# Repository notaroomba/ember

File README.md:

<h1 align="center">
  <br>
  
  <br>
  Ember
  <br>
</h1>

<h4 align="center">
A high-performance USB-C powered reflow hotplate with Bluetooth connectivity and intelligent temperature control!
</h4>

<div align="center">

</div>

<p align="center">
  <a href="#key-features">Key Features</a> •
  <a href="#pcb">PCB</a> •
  <a href="#case">Case</a> •
  <a href="#heatbed">Heatbed</a> •
  <a href="#credits">Credits</a> •
  <a href="#license">License</a>
</p>

<!--  -->

## Key Features

- **USB-C Power Delivery** up to 100W (20V) using TI's TPS25730D
- **STM32WB55CG** microcontroller with Bluetooth support
- **Large ~~400mm x 400mm~~ ~~200mm x 200mm~~ 120mm x 120mm (for now) flexible heatbed** for big PCB reflow
- **Dual temperature sensing** with MAX6675 thermocouple and PT1000 RTD
- **OLED display** with rotary encoder for easy control and preset management
- **NFC support** for wireless temperature profile transfer and preset storage
- **Gate driver** for precise PWM heatbed control
- **Current and board temperature monitoring** for safety
- **32MB Flash memory** for graphics and data storage
- **Portable design** with custom acrylic / nylon case

## PCB

Designed in KiCad!

### Schematic

### PCB Layout

**Front:**

**Back:**

**Ground Plane:**

**Power Plane:**

Board dimensions: 50mm x 150mm

## Case

Custom designed case in OnShape with practical features:

Features:
- **USB-C port cutout** with flush cable routing
- **Screw terminal access** for heatbed and temperature sensor connections
- **Heatset inserts** for secure assembly with slotted cylindrical head screws
- **High-quality materials**: PA11-HP Nylon base with acrylic top for visibility
- **Rounded corners** for aesthetics and safety

## Heatbed

The heatbed uses JLCPCB's flexible heater technology for cost-effective large-area heating.

The flexible heater connects to the main PCB via screw terminals!

## 3D Renders

## Credits

This project uses:

- [KiCad](https://www.kicad.org/)
- [OnShape](https://www.onshape.com/) for case design
- [Blender](https://www.blender.org/) for 3D renders
- [STM32CubeMX](https://www.st.com/en/development-tools/stm32cubemx.html)
- Inspiration from [this reflow hotplate project](https://github.com/ikajdan/reflow-hot-plate)
- [Arduino GFX Tool](https://arduinogfxtool.netlify.app/) for OLED UI/UX design

## You may also like...

- [Cyberboard](https://github.com/NotARoomba/Cyberboard) – A Raspberry Pi Pico-sized STM32 development board with Bluetooth
- [Trace](https://github.com/NotARoomba/Trace) – A comprehensive PCB ruler with reference footprints
- [CyberCard](https://github.com/NotARoomba/CyberCard) – A Cyberpunk themed NFC hacker card
- [Niveles De Niveles](https://github.com/NotARoomba/NivelesDeNiveles) – Real-time flood alert app
- [Linea](https://github.com/NotARoomba/Linea) – An EMR tablet
- [Tamaki](https://github.com/NotARoomba/Tamaki) – A cute HackPad

## License

MIT

---

> [notaroomba.dev](https://notaroomba.dev) &nbsp;&middot;&nbsp;
> GitHub [@NotARoomba](https://github.com/NotARoomba) &nbsp;&middot;&nbsp;

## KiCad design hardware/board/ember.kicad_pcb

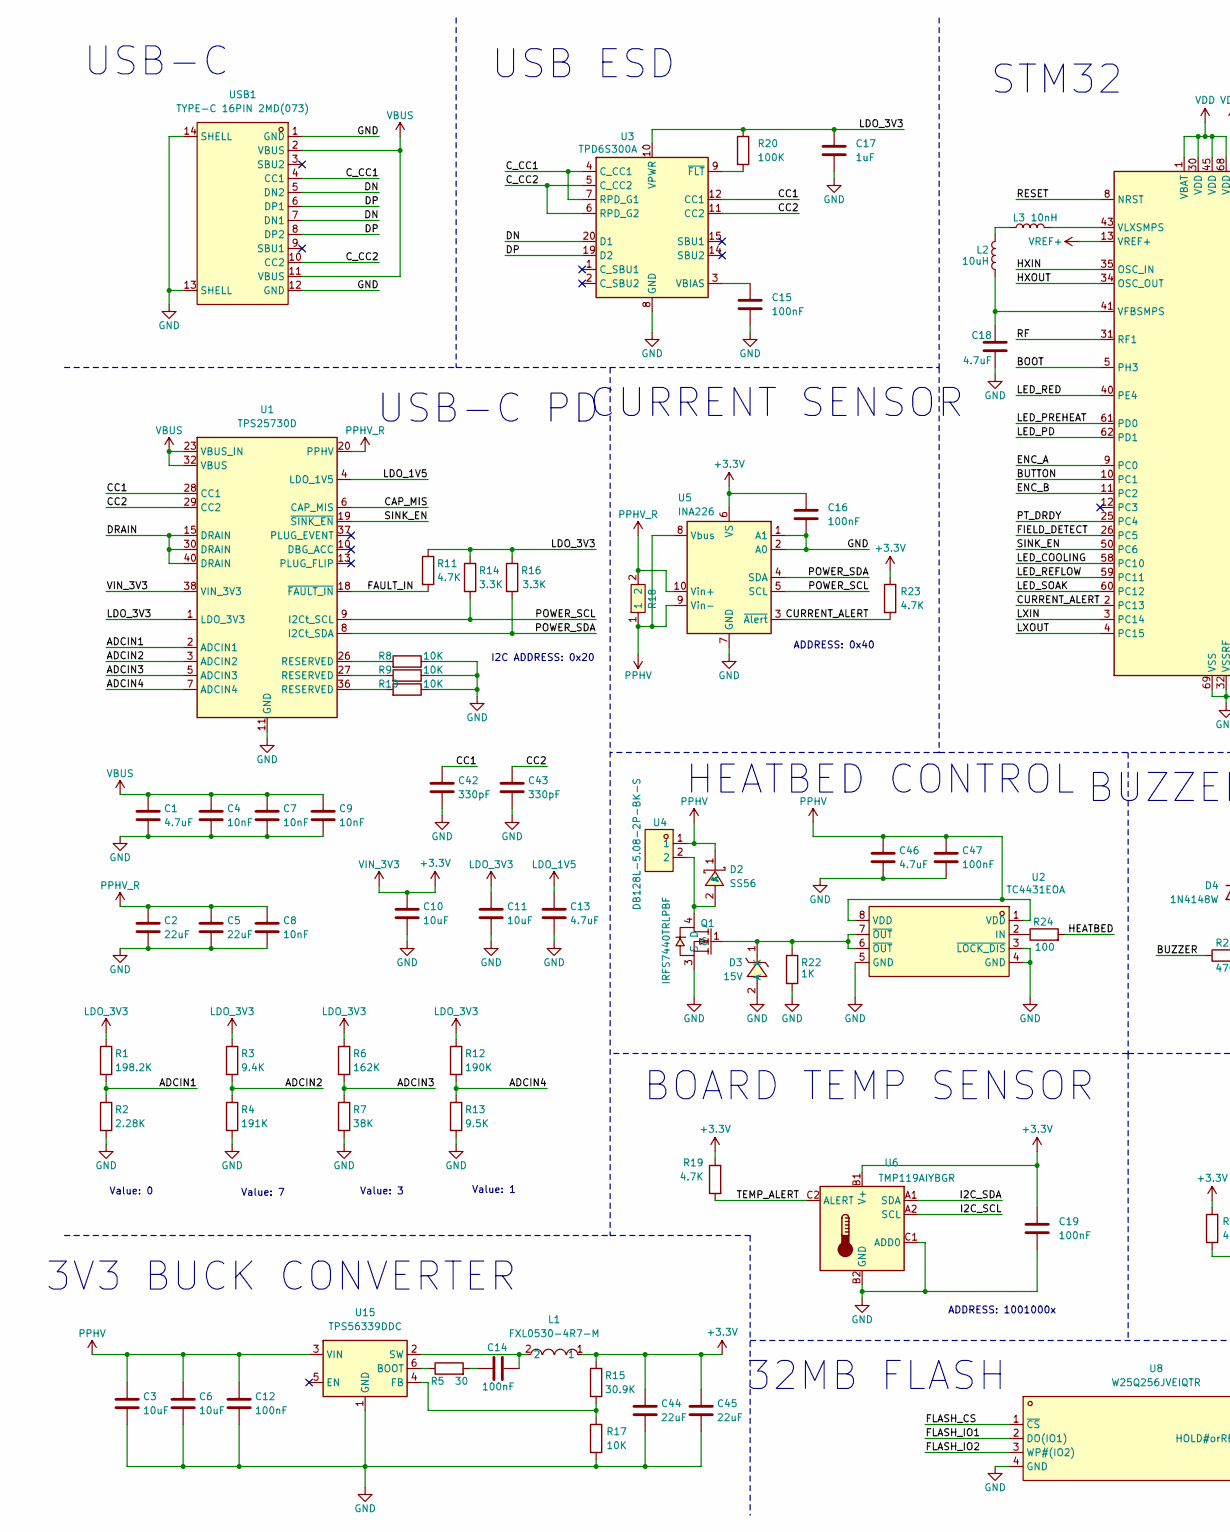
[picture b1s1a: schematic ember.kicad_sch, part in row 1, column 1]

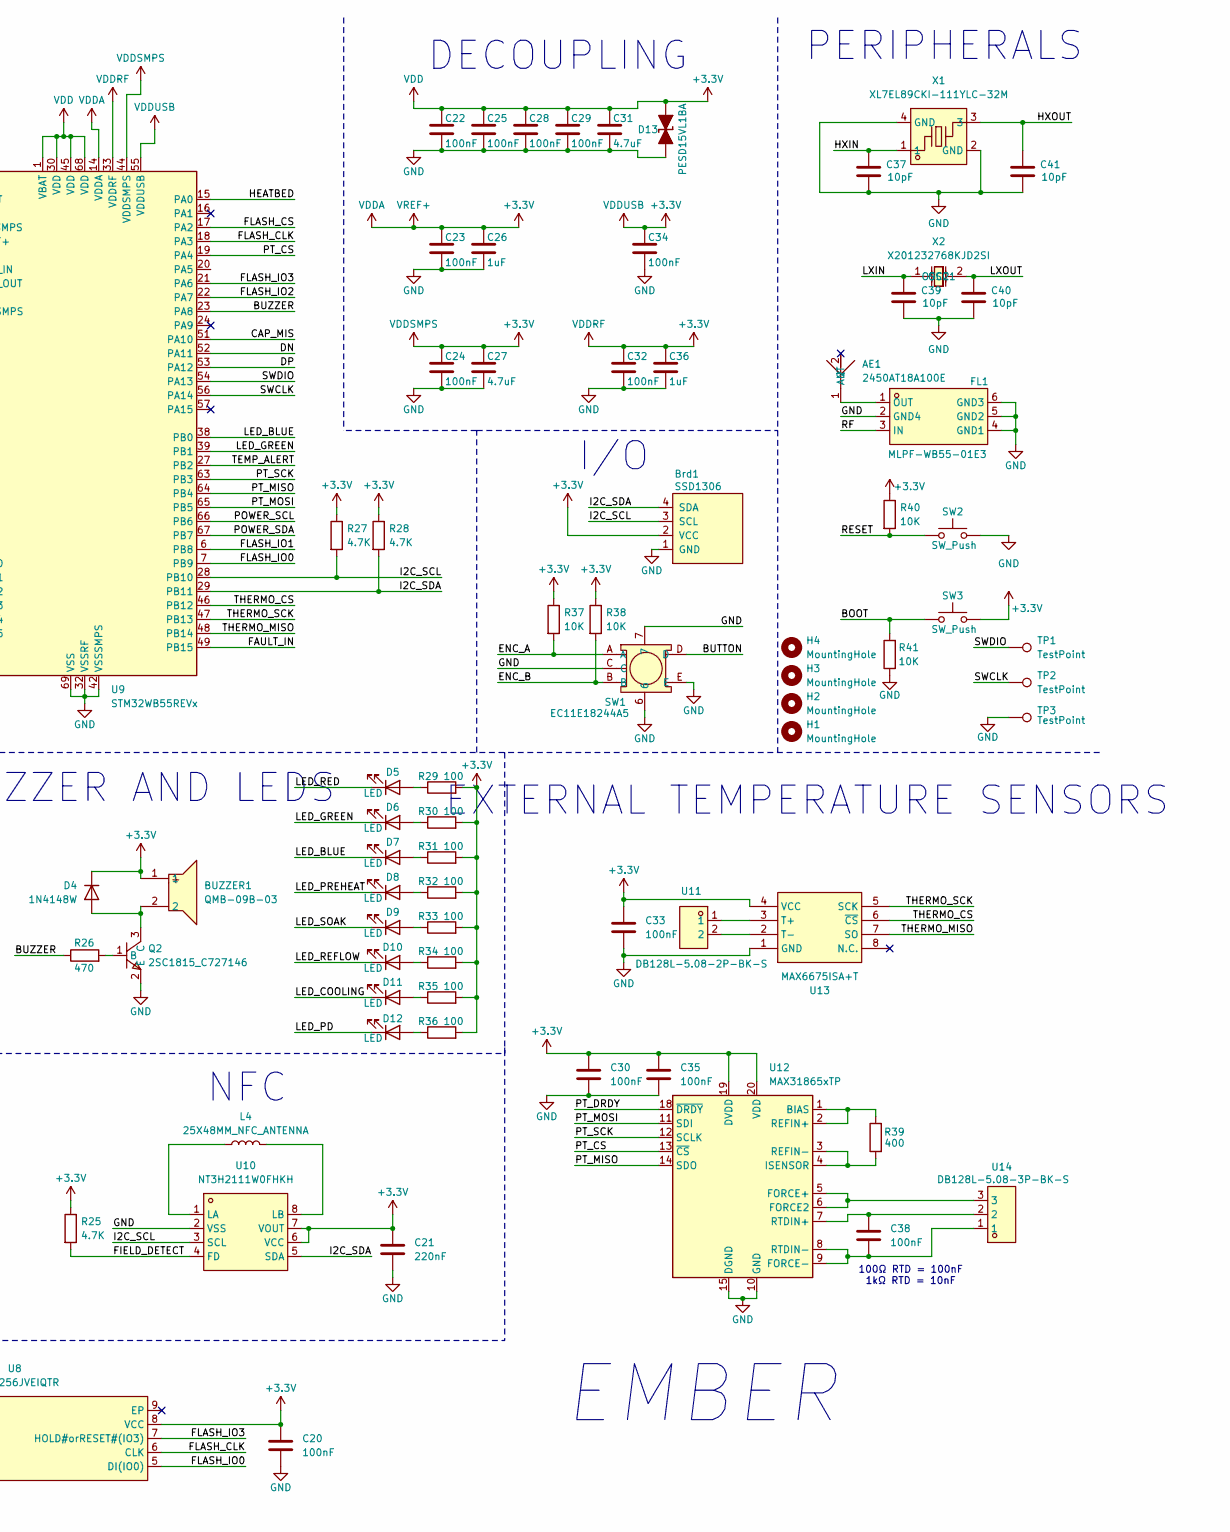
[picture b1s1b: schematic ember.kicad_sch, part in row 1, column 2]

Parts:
AE1: 2450AT18A100E; ANT-SMD_L3.2-W1.6; LCSC Part C89334
BUZZER1: QMB-09B-03; BUZ-TH_BD9.0-P4.00-D0.6-FD; LCSC Part C96256
Brd1: SSD1306; 128x64OLED
C1: 4.7uF; C_0805_2012Metric
C2, C5, C44, C45: 22uF; C_0805_2012Metric
C3, C6: 10uF; C_0805_2012Metric
C4, C7, C9: 10nF; C_0603_1608Metric
C8: 10nF; C_0402_1005Metric
C10, C11: 10uF; C_0402_1005Metric
C12, C47: 100nF; C_0603_1608Metric
C13: 4.7uF; C_0402_1005Metric
C14, C15, C16, C19, C20, C22, C23, C24, C25, C28, C29, C30, C32, C33, C34, C35, C38: 100nF; C_0402_1005Metric
C17: 1uF; C_0402_1005Metric
C18, C27, C31, C46: 4.7uF; C_0603_1608Metric
C21: 220nF; C_0603_1608Metric; LCSC C21120
C26, C36: 1uF; C_0603_1608Metric
C37, C39, C40, C41: 10pF; C_0402_1005Metric
C42, C43: 330pF; C_0402_1005Metric
D2: SS56; SMA_L4.3-W2.6-LS5.2-RD; LCSC Part C65009
D3: 15V; SOD-323_L1.7-W1.3-LS2.6-RD; LCSC Part C19077448
D4: 1N4148W; D_SOD-123
D5: LED; LED_0603_1608Metric; LCSC C965799
D6: LED; LED_0603_1608Metric; LCSC C19171301
D7: LED; LED_0603_1608Metric; LCSC C965807
D8, D9, D10, D11: LED; LED_0603_1608Metric; LCSC C965800
D12: LED; LED_0603_1608Metric; LCSC C2290
D13: PESD15VL1BA; D_SOD-323
FL1: MLPF-WB55-01E3; FILTER-SMD_6P-L1.6-W1.0-P0.50-BL; LCSC Part C2651048
H1, H2, H3, H4: MountingHole; MountingHole_2.2mm_M2
L1: FXL0530-4R7-M; IND-SMD_L5.4-W5.2_FXL0530; LCSC Part C177246
L2: 10uH; L_0603_1608Metric
L3: 10nH; L_0603_1608Metric
L4: 25X48MM_NFC_ANTENNA
Q1: IRFS7440TRLPBF; TO-263-2_L10.0-W9.1-P5.08-LS15.2-BR; LCSC Part C409762
Q2: 2SC1815_C727146; SOT-23-3_L2.9-W1.3-P1.90-LS2.4-BR; LCSC Part C727146
R1: 198.2K; R_0402_1005Metric; LCSC C3013157
R2: 2.28K; R_0402_1005Metric; LCSC C2998174
R3: 9.4K; R_0402_1005Metric; LCSC C852970
R4: 191K; R_0402_1005Metric; LCSC C2998070
R5: 30; R_0402_1005Metric
R6: 162K; R_0402_1005Metric
R7: 38K; R_0402_1005Metric; LCSC C852750
R8, R9, R10, R17, R37, R38, R40, R41: 10K; R_0402_1005Metric
R11, R19, R23, R25, R27, R28: 4.7K; R_0402_1005Metric
R12: 190K; R_0402_1005Metric; LCSC C2998070
R13: 9.5K; R_0402_1005Metric; LCSC C96273
R14, R16: 3.3K; R_0402_1005Metric
R15: 30.9K; R_0402_1005Metric
R18: HOLLR2512-3W-2MR-1%; RES-SMD_L6.4-W3.2-1; LCSC Part C2994640
R20: 100K; R_0402_1005Metric
R22: 1K; R_0402_1005Metric
R24, R29, R30, R31, R32, R33, R34, R35, R36: 100; R_0402_1005Metric
R26: 470; R_0402_1005Metric
R39: 400; R_0805_2012Metric; LCSC C153298
SW1: EC11E18244A5; SW-TH_EC11E18244A5; LCSC Part C255515
SW2, SW3: SW_Push; SW-SMD_L3.9-W3.0-P4.45; LCSC C720477
TP1, TP2, TP3: TestPoint; TestPoint_Pad_1.0x1.0mm
U1: TPS25730D; Texas_REF0038A_WQFN-38-2EP_6x4mm_P0.4
U2: TC4431EOA; SOIC-8_L4.9-W3.9-P1.27-LS6.0-BL; LCSC Part C2909520
U3: TPD6S300A; WQFN-20-1EP_3x3mm_P0.4mm_EP1.7x1.7mm_ThermalVias
U4, U11: DB128L-5.08-2P-BK-S; CONN-TH_2P-P5.08_DB128L-5.08-2P-BK-S; LCSC Part C430601
U5: INA226; VSSOP-10_3x3mm_P0.5mm
U6: TMP119AIYBGR; Texas_DSBGA-6_0.95x1.488mm_Layout2x3_P0.4mm
U8: W25Q256JVEIQTR; WSON-8_L8.0-W6.10-P1.27-BL-EP; LCSC Part C97522
U9: STM32WB55REVx; QFN-68-1EP_8x8mm_P0.4mm_EP6.4x6.4mm
U10: NT3H2111W0FHKH; XQFN-8_L1.6-W1.6-P0.50-BL_NT3H2111W0FHKH; LCSC Part C710403
U12: MAX31865xTP; TQFN-20-1EP_5x5mm_P0.65mm_EP3.25x3.25mm
U13: MAX6675ISA+T; SOIC-8_L5.0-W4.0-P1.27-LS6.0-BL; LCSC Part C16030
U14: DB128L-5.08-3P-BK-S; CONN-TH_3P-P5.08_DB128L-5.08-3P-BK-S; LCSC Part C430602
U15: TPS56339DDC; SOT-23-6
USB1: TYPE-C 16PIN 2MD(073); USB-C-SMD_TYPE-C-6PIN-2MD-073; LCSC Part C2765186
X1: XL7EL89CKI-111YLC-32M; CRYSTAL-SMD_4P-L2.0-W1.6-BL; LCSC Part C2965582
X2: X201232768KJD2SI; OSC-SMD_L2.0-W1.2; LCSC Part C383843

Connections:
+3.3V: BUZZER1.1, Brd1.2 (VCC), C10.1, C16.1, C19.1, C20.1, C21.2, C22.1, C23.1, C24.1, C25.1, C26.1, C27.1, C28.1, C29.1, C30.1, C31.1, C32.1, C33.1, C34.1, C35.1, C36.1, C44.1, C45.1, D4.1 (K), D13.2 (A), L1.1, R15.1, R19.1, R23.1, R25.1, R27.1, R28.1, R29.2, R30.2, R31.2, R32.2, R33.2, R34.2, R35.2, R36.2, R37.1, R38.1, R40.1, SW3.2, U1.38 (VIN_3V3), U5.6 (VS), U6.B1 (V+), U8.8 (VCC), U9.1 (VBAT), U9.13 (VREF+), U9.14 (VDDA), U9.30 (VDD), U9.33 (VDDRF), U9.44 (VDDSMPS), U9.45 (VDD), U9.55 (VDDUSB), U9.68 (VDD), U10.6 (VCC), U10.7 (VOUT), U12.19 (DVDD), U12.20 (VDD), U13.4 (VCC)
/ADCIN1: R1.2, R2.1, U1.2 (ADCIN1)
/ADCIN2: R3.2, R4.1, U1.3 (ADCIN2)
/ADCIN3: R6.2, R7.1, U1.5 (ADCIN3)
/ADCIN4: R12.2, R13.1, U1.7 (ADCIN4)
/BOOT: R41.2, SW3.1, U9.5 (PH3)
/BUTTON: SW1.D, U9.10 (PC1)
/BUZZER: R26.1, U9.23 (PA8)
/CAP_MIS: U1.6 (CAP_MIS), U9.51 (PA10)
/CC1: C42.1, U1.28 (CC1), U3.12 (CC1)
/CC2: C43.1, U1.29 (CC2), U3.11 (CC2)
/CURRENT_ALERT: R23.2, U5.3 (~Alert), U9.2 (PC13)
/C_CC1: U3.4 (C_CC1), U3.7 (RPD_G1), USB1.4 (CC1)
/C_CC2: U3.5 (C_CC2), U3.6 (RPD_G2), USB1.10 (CC2)
/DN: U3.20 (D1), U9.52 (PA11), USB1.5 (DN2), USB1.7 (DN1)
/DP: U3.19 (D2), U9.53 (PA12), USB1.6 (DP1), USB1.8 (DP2)
/DRAIN: U1.15 (DRAIN), U1.30 (DRAIN), U1.40 (DRAIN)
/ENC_A: R37.2, SW1.A, U9.9 (PC0)
/ENC_B: R38.2, SW1.B, U9.11 (PC2)
/FAULT_IN: R11.2, U1.18 (~FAULT_IN), U9.49 (PB15)
/FIELD_DETECT: R25.2, U9.26 (PC5), U10.4 (FD)
/FLASH_CLK: U8.6 (CLK), U9.18 (PA3)
/FLASH_CS: U8.1 (~CS), U9.17 (PA2)
/FLASH_IO0: U8.5 (DI(IO0)), U9.7 (PB9)
/FLASH_IO1: U8.2 (DO(IO1)), U9.6 (PB8)
/FLASH_IO2: U8.3 (WP#(IO2)), U9.22 (PA7)
/FLASH_IO3: U8.7 (HOLD#orRESET#(IO3)), U9.21 (PA6)
/HEATBED: R24.2, U9.15 (PA0)
/HXIN: C37.1, U9.35 (OSC_IN), X1.1
/HXOUT: C41.1, U9.34 (OSC_OUT), X1.3
/I2C_SCL: Brd1.3 (SCL), R27.2, U6.A2 (SCL), U9.28 (PB10), U10.3 (SCL)
/I2C_SDA: Brd1.4 (SDA), R28.2, U6.A1 (SDA), U9.29 (PB11), U10.5 (SDA)
/LED_BLUE: D7.1 (K), U9.38 (PB0)
/LED_COOLING: D11.1 (K), U9.58 (PC10)
/LED_GREEN: D6.1 (K), U9.39 (PB1)
/LED_PD: D12.1 (K), U9.62 (PD1)
/LED_PREHEAT: D8.1 (K), U9.61 (PD0)
/LED_RED: D5.1 (K), U9.40 (PE4)
/LED_REFLOW: D10.1 (K), U9.59 (PC11)
/LED_SOAK: D9.1 (K), U9.60 (PC12)
/LXIN: C39.1, U9.3 (PC14), X2.1 (OSC1)
/LXOUT: C40.1, U9.4 (PC15), X2.2 (OSC2)
/POWER_SCL: R14.2, U1.9 (I2Ct_SCL), U5.5 (SCL), U9.66 (PB6)
/POWER_SDA: R16.2, U1.8 (I2Ct_SDA), U5.4 (SDA), U9.67 (PB7)
/PT_CS: U9.19 (PA4), U12.13 (~CS)
/PT_DRDY: U9.25 (PC4), U12.18 (~DRDY)
/PT_MISO: U9.64 (PB4), U12.14 (SDO)
/PT_MOSI: U9.65 (PB5), U12.11 (SDI)
/PT_SCK: U9.63 (PB3), U12.12 (SCLK)
/RESET: R40.2, SW2.1, U9.8 (NRST)
/RF: FL1.3 (IN), U9.31 (RF1)
/SINK_EN: U1.19 (~SINK_EN), U9.50 (PC6)
/SWCLK: TP2.1, U9.56 (PA14)
/SWDIO: TP1.1, U9.54 (PA13)
/TEMP_ALERT: R19.2, U6.C2 (ALERT), U9.27 (PB2)
/THERMO_CS: U9.46 (PB12), U13.6 (~CS)
/THERMO_MISO: U9.48 (PB14), U13.7 (SO)
/THERMO_SCK: U9.47 (PB13), U13.5 (SCK)
GND: Brd1.1 (GND), C1.2, C2.2, C3.2, C4.2, C5.2, C6.2, C7.2, C8.2, C9.2, C10.2, C11.2, C12.2, C13.2, C15.2, C16.2, C17.2, C18.2, C19.2, C20.2, C21.1, C22.2, C23.2, C24.2, C25.2, C26.2, C27.2, C28.2, C29.2, C30.2, C31.2, C32.2, C33.2, C34.2, C35.2, C36.2, C37.2, C39.2, C40.2, C41.2, C42.2, C43.2, C44.2, C45.2, C46.2, C47.2, D3.2 (A), D13.1 (K), FL1.2 (GND4), FL1.4 (GND1), FL1.5 (GND2), FL1.6 (GND3), Q1.3 (S), Q2.2 (E), R2.2, R4.2, R7.2, R8.1, R9.1, R10.1, R13.2, R17.2, R22.2, R41.1, SW1.6, SW1.7, SW1.C, SW1.E, SW2.2, TP3.1, U1.11 (GND), U1.12 (GND), U1.14 (GND), U1.16 (GND), U1.17 (GND), U1.31 (GND), U1.34 (GND), U1.39 (GND), U2.3 (~LOCK_DIS), U2.4 (GND), U2.5 (GND), U3.8 (GND), U3.13 (GND), U3.16 (GND), U3.17 (GND), U3.18 (GND), U3.21 (GND), U5.1 (A1), U5.2 (A0), U5.7 (GND), U6.B2 (GND), U6.C1 (ADD0), U8.4 (GND), U8.9 (EP), U9.32 (VSSRF), U9.42 (VSSSMPS), U9.69 (VSS), U10.2 (VSS), U12.10 (GND), U12.15 (DGND), U12.16 (GND), U12.21 (GND), U13.1 (GND), U15.1 (GND), USB1.1 (GND), USB1.12 (GND), USB1.13 (SHELL), USB1.14 (SHELL), X1.2 (GND), X1.4 (GND)
LDO_1V5: C13.1, U1.4 (LDO_1V5)
LDO_3V3: C11.1, C17.1, R1.1, R3.1, R6.1, R11.1, R12.1, R14.1, R16.1, R20.1, U1.1 (LDO_3V3), U3.10 (VPWR)
unnamed: AE1.1 (ANT), FL1.1 (OUT)
unnamed: C14.1, R5.2
unnamed: D2.2 (A), Q1.4 (D), U4.2
unnamed: D3.1 (K), Q1.1 (G), R22.1, U2.6 (~OUT), U2.7 (~OUT)
unnamed: BUZZER1.2, D4.2 (A), Q2.3 (C)
unnamed: D5.2 (A), R29.1
unnamed: D6.2 (A), R30.1
unnamed: D7.2 (A), R31.1
unnamed: D8.2 (A), R32.1
unnamed: D9.2 (A), R33.1
unnamed: D10.2 (A), R34.1
unnamed: D11.2 (A), R35.1
unnamed: D12.2 (A), R36.1
unnamed: L2.1, L3.2
unnamed: Q2.1 (B), R26.2
unnamed: R8.2, U1.26 (RESERVED)
unnamed: R9.2, U1.27 (RESERVED)
unnamed: R10.2, U1.36 (RESERVED)
unnamed: R24.1, U2.2 (IN)
unnamed: C15.1, U3.3 (VBIAS)
unnamed: R20.2, U3.9 (~FLT)
unnamed: C18.1, L2.2, U9.41 (VFBSMPS)
unnamed: L3.1, U9.43 (VLXSMPS)
unnamed: L4.1, U10.1 (LA)
unnamed: L4.2, U10.8 (LB)
unnamed: R39.1, U12.1 (BIAS), U12.2 (REFIN+)
unnamed: U12.5 (FORCE+), U12.6 (FORCE2), U14.3
unnamed: C38.2, U12.8 (RTDIN-), U12.9 (FORCE-), U14.1
unnamed: R39.2, U12.3 (REFIN-), U12.4 (ISENSOR)
unnamed: C38.1, U12.7 (RTDIN+), U14.2
unnamed: U11.1, U13.3 (T+)
unnamed: U11.2, U13.2 (T-)
unnamed: R5.1, U15.6 (BOOT)
unnamed: R15.2, R17.1, U15.4 (FB)
unnamed: C14.2, L1.2, U15.2 (SW)
PPHV: C3.1, C6.1, C12.1, C46.1, C47.1, D2.1 (K), R18.1, U2.1 (VDD), U2.8 (VDD), U4.1, U5.8 (Vbus), U5.9 (Vin-), U15.3 (VIN)
PPHV_R: C2.1, C5.1, C8.1, R18.2, U1.20 (PPHV), U5.10 (Vin+)
VBUS: C1.1, C4.1, C7.1, C9.1, U1.23 (VBUS_IN), U1.32 (VBUS), USB1.2 (VBUS), USB1.11 (VBUS)

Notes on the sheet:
I/O
EXTERNAL TEMPERATURE SENSORS
PERIPHERALS
EMBER
BUZZER AND LEDS
USB-C
100Ω RTD = 100nF 1kΩ RTD = 10nF
USB ESD
USB-C PD
Value: 7
Value: 1
BOARD TEMP SENSOR
DECOUPLING
NFC
32MB FLASH
CURRENT SENSOR
ADDRESS: 0x40
3V3 BUCK CONVERTER
ADDRESS: 1001000x
HEATBED CONTROL
Value: 0
I2C ADDRESS: 0x20
STM32
Value: 3

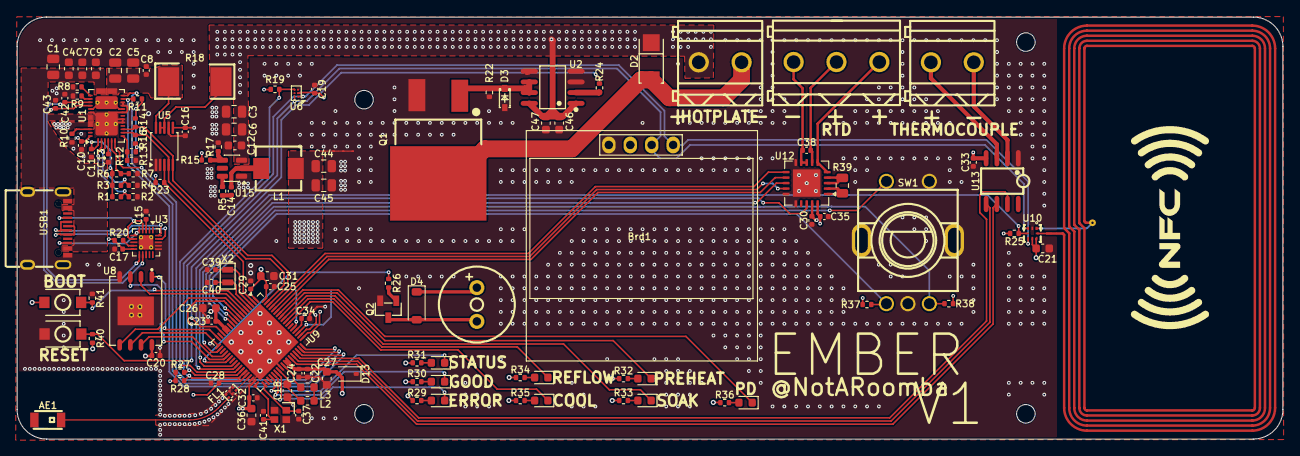
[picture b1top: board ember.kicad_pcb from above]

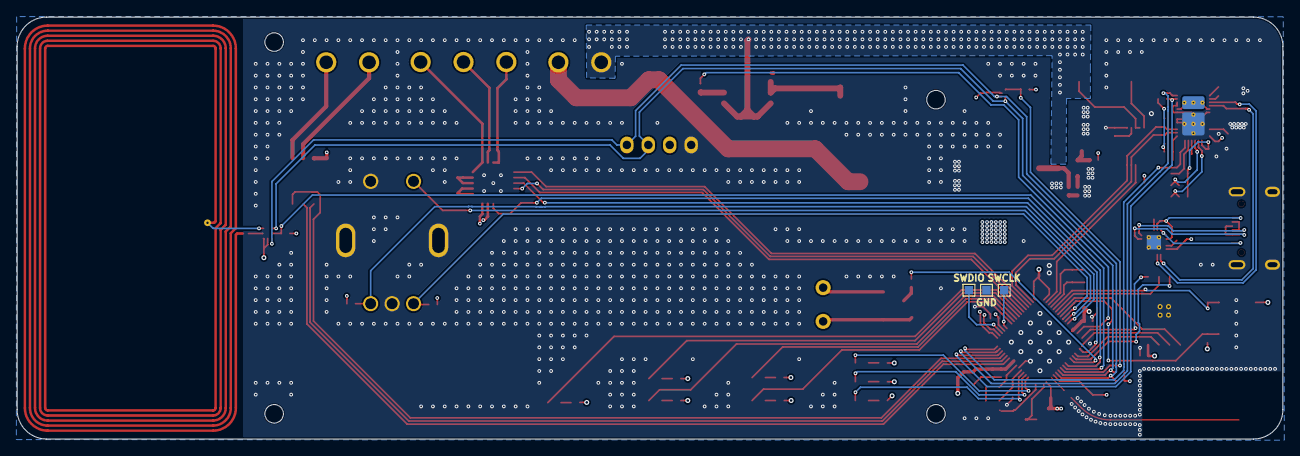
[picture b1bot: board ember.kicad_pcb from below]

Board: 4 copper layers, 150.0 x 50.0 mm, 136 parts (3 on the bottom side), 97 nets.

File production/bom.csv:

Designator,Footprint,Quantity,Value,LCSC Part #
AE1,ANT-SMD_L3.2-W1.6,1,2450AT18A100E,C89334
BRD1,128x64OLED,1,SSD1306,
BUZZER1,BUZ-TH_BD9.0-P4.00-D0.6-FD,1,QMB-09B-03,C96256
C1,0805,1,4.7uF,
"C10, C11",0402,2,10uF,
"C12, C47",0603,2,100nF,
C13,0402,1,4.7uF,
"C14, C15, C16, C19, C20, C22, C23, C24, C25, C28, C29, C30, C32, C33, C34, C35, C38",0402,17,100nF,
C17,0402,1,1uF,
"C18, C27, C31, C46",0603,4,4.7uF,
"C2, C44, C45, C5",0805,4,22uF,
C21,0603,1,220nF,C21120
"C26, C36",0603,2,1uF,
"C3, C6",0805,2,10uF,
"C37, C39, C40, C41",0402,4,10pF,
"C4, C7, C9",0603,3,10nF,
"C42, C43",0402,2,330pF,
C8,0402,1,10nF,
"D10, D11, D8, D9",0603,4,LED,C965800
D12,0603,1,LED,C2290
D13,D_SOD-323,1,PESD15VL1BA,
D2,SMA_L4.3-W2.6-LS5.2-RD,1,SS56,C65009
D3,SOD-323_L1.7-W1.3-LS2.6-RD,1,15V,C19077448
D4,D_SOD-123,1,1N4148W,
D5,0603,1,LED,C965799
D6,0603,1,LED,C19171301
D7,0603,1,LED,C965807
FL1,FILTER-SMD_6P-L1.6-W1.0-P0.50-BL,1,MLPF-WB55-01E3,C2651048
L1,IND-SMD_L5.4-W5.2_FXL0530,1,FXL0530-4R7-M,C177246
L2,0603,1,10uH,
L3,0603,1,10nH,
L4,25X48MM_NFC_ANTENNA,1,25X48MM_NFC_ANTENNA,
Q1,TO-263-2_L10.0-W9.1-P5.08-LS15.2-BR,1,IRFS7440TRLPBF,C409762
Q2,SOT-23-3_L2.9-W1.3-P1.90-LS2.4-BR,1,2SC1815_C727146,C727146
R1,0402,1,198.2K,C3013157
"R10, R17, R37, R38, R40, R41, R8, R9",0402,8,10K,
"R11, R19, R23, R25, R27, R28",0402,6,4.7K,
R12,0402,1,190K,C2998070
R13,0402,1,9.5K,C96273
"R14, R16",0402,2,3.3K,
R15,0402,1,30.9K,
R18,RES-SMD_L6.4-W3.2-1,1,HOLLR2512-3W-2MR-1%,C2994640
R2,0402,1,2.28K,C2998174
R20,0402,1,100K,
R22,0402,1,1K,
"R24, R29, R30, R31, R32, R33, R34, R35, R36",0402,9,100,
R26,0402,1,470,
R3,0402,1,9.4K,C852970
R39,0805,1,400,C153298
R4,0402,1,191K,C2998070
R5,0402,1,30,
R6,0402,1,162K,
R7,0402,1,38K,C852750
SW1,SW-TH_EC11E18244A5,1,EC11E18244A5,C255515
"SW2, SW3",SW-SMD_L3.9-W3.0-P4.45,2,SW_Push,C720477
"TP1, TP2, TP3",TestPoint_Pad_1.0x1.0mm,3,TestPoint,
U1,Texas_REF0038A_WQFN-38-2EP_6x4mm_P0.4,1,TPS25730D,
U10,XQFN-8_L1.6-W1.6-P0.50-BL_NT3H2111W0FHKH,1,NT3H2111W0FHKH,C710403
"U11, U4",CONN-TH_2P-P5.08_DB128L-5.08-2P-BK-S,2,DB128L-5.08-2P-BK-S,C430601
U12,TQFN-20-1EP_5x5mm_P0.65mm_EP3.25x3.25mm,1,MAX31865xTP,
U13,SOIC-8_L5.0-W4.0-P1.27-LS6.0-BL,1,MAX6675ISA+T,C16030
U14,CONN-TH_3P-P5.08_DB128L-5.08-3P-BK-S,1,DB128L-5.08-3P-BK-S,C430602
U15,SOT-23-6,1,TPS56339DDC,
U2,SOIC-8_L4.9-W3.9-P1.27-LS6.0-BL,1,TC4431EOA,C2909520
U3,WQFN-20-1EP_3x3mm_P0.4mm_EP1.7x1.7mm_ThermalVias,1,TPD6S300A,
U5,VSSOP-10_3x3mm_P0.5mm,1,INA226,
U6,Texas_DSBGA-6_0.95x1.488mm_Layout2x3_P0.4mm,1,TMP119AIYBGR,
U8,WSON-8_L8.0-W6.10-P1.27-BL-EP,1,W25Q256JVEIQTR,C97522
U9,QFN-68-1EP_8x8mm_P0.4mm_EP6.4x6.4mm,1,STM32WB55REVx,
USB1,USB-C-SMD_TYPE-C-6PIN-2MD-073,1,TYPE-C 16PIN 2MD(073),C2765186
X1,CRYSTAL-SMD_4P-L2.0-W1.6-BL,1,XL7EL89CKI-111YLC-32M,C2965582
X2,OSC-SMD_L2.0-W1.2,1,X201232768KJD2SI,C383843

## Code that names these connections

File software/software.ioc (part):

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Mcu.Name=STM32WB55REVx
Mcu.Package=VFQFPN68
Mcu.UserName=STM32WB55REVx
PA0.GPIOParameters=GPIO_Label
PA0.GPIO_Label=HEATBED
PA0.Signal=S_TIM2_CH1
PA11.Mode=Device
PA11.Signal=USB_DM
PA12.Mode=Device
PA12.Signal=USB_DP
PA13.Mode=Serial_Wire
PA13.Signal=SYS_JTMS-SWDIO
PA14.Mode=Serial_Wire
PA14.Signal=SYS_JTCK-SWCLK
PA2.Mode=Single Bank 1
PA2.Signal=QUADSPI_BK1_NCS
PA3.Mode=Single Bank 1
PA3.Signal=QUADSPI_CLK
PA4.GPIOParameters=GPIO_Label
PA4.GPIO_Label=PT_CS
PA4.Mode=NSS_Signal_Hard_Output
PA4.Signal=SPI1_NSS
PA6.Mode=Single Bank 1
PA6.Signal=QUADSPI_BK1_IO3
PA7.Mode=Single Bank 1
PA7.Signal=QUADSPI_BK1_IO2
PA8.GPIOParameters=GPIO_Label
PA8.GPIO_Label=BUZZER
PA8.Signal=S_TIM1_CH1
PB0.GPIOParameters=GPIO_Label
PB0.GPIO_Label=LED_BLUE
PB0.Signal=GPIO_Output
PB1.GPIOParameters=GPIO_Label
PB1.GPIO_Label=LED_GREEN
PB1.Signal=GPIO_Output
PB10.GPIOParameters=GPIO_Label
PB10.GPIO_Label=I2C_SCL
PB10.Mode=I2C
PB10.Signal=I2C3_SCL
PB11.GPIOParameters=GPIO_Label
PB11.GPIO_Label=I2C_SDA
PB11.Mode=I2C
PB11.Signal=I2C3_SDA
PB12.GPIOParameters=GPIO_Label
PB12.GPIO_Label=THERMO_CS
PB12.Mode=NSS_Signal_Hard_Output
PB12.Signal=SPI2_NSS
PB13.GPIOParameters=GPIO_Label
PB13.GPIO_Label=THERMO_SCK
PB13.Mode=RX_Only_Simplex_Unidirect_Master
PB13.Signal=SPI2_SCK
PB14.GPIOParameters=GPIO_Label
PB14.GPIO_Label=THERMO_MISO
PB14.Mode=RX_Only_Simplex_Unidirect_Master
PB14.Signal=SPI2_MISO
PB15.GPIOParameters=GPIO_Label
PB15.GPIO_Label=FAULT_IN
PB15.Signal=GPIO_Input
PB2.GPIOParameters=GPIO_Label
PB2.GPIO_Label=TEMP_ALERT
PB2.Signal=GPXTI2
PB3.GPIOParameters=GPIO_Label
PB3.GPIO_Label=PT_SCK
PB3.Mode=Full_Duplex_Master
PB3.Signal=SPI1_SCK
PB4.GPIOParameters=GPIO_Label
PB4.GPIO_Label=PT_MISO
PB4.Mode=Full_Duplex_Master
PB4.Signal=SPI1_MISO
PB5.GPIOParameters=GPIO_Label
PB5.GPIO_Label=PT_MOSI
PB5.Mode=Full_Duplex_Master
PB5.Signal=SPI1_MOSI
PB6.GPIOParameters=GPIO_Label
PB6.GPIO_Label=POWER_SCL
PB6.Mode=I2C
PB6.Signal=I2C1_SCL
PB7.GPIOParameters=GPIO_Label
PB7.GPIO_Label=POWER_SDA
PB7.Mode=I2C
PB7.Signal=I2C1_SDA
PB8.Mode=Single Bank 1
PB8.Signal=QUADSPI_BK1_IO1
PB9.Mode=Single Bank 1
PB9.Signal=QUADSPI_BK1_IO0
PC0.GPIOParameters=GPIO_Label
PC0.GPIO_Label=ENC_A
PC0.Mode=Encoder_mode_occur1
PC0.Signal=LPTIM1_IN1
PC1.GPIOParameters=GPIO_PuPd,GPIO_Label
PC1.GPIO_Label=BUTTON
PC1.GPIO_PuPd=GPIO_PULLUP
PC1.Signal=GPIO_Input
PC10.GPIOParameters=GPIO_Label
PC10.GPIO_Label=LED_COOLING
PC10.Signal=GPIO_Output
PC11.GPIOParameters=GPIO_Label
PC11.GPIO_Label=LED_REFLOW
PC11.Signal=GPIO_Output
PC12.GPIOParameters=GPIO_Label
PC12.GPIO_Label=LED_SOAK
PC12.Signal=GPIO_Output
PC13.GPIOParameters=GPIO_Label
PC13.GPIO_Label=CURRENT_ALERT
PC13.Signal=GPXTI13
PC14-OSC32_IN.Mode=LSE-External-Oscillator
PC14-OSC32_IN.Signal=RCC_OSC32_IN
PC15-OSC32_OUT.Mode=LSE-External-Oscillator
PC15-OSC32_OUT.Signal=RCC_OSC32_OUT
PC2.GPIOParameters=GPIO_Label
PC2.GPIO_Label=ENC_B
PC2.Mode=Encoder_mode_occur1
PC2.Signal=LPTIM1_IN2
PC4.GPIOParameters=GPIO_Label
PC4.GPIO_Label=PT_DRDY
PC4.Signal=GPXTI4
PC5.GPIOParameters=GPIO_Label
PC5.GPIO_Label=FIELD_DETECT
PC5.Signal=GPIO_Input
PC6.GPIOParameters=GPIO_Label
PC6.GPIO_Label=SINK_EN
PC6.Signal=GPIO_Input
PD0.GPIOParameters=GPIO_Label
PD0.GPIO_Label=LED_PREHEAT
PD0.Signal=GPIO_Output
PD1.GPIOParameters=GPIO_Label
PD1.GPIO_Label=LED_PD
PD1.Signal=GPIO_Output
PE4.GPIOParameters=GPIO_Label
PE4.GPIO_Label=LED_RED
PE4.Signal=GPIO_Output
RCC.HSE_VALUE=32000000
RCC.SYSCLKFreq_VALUE=64000000
RCC.SYSCLKSource=RCC_SYSCLKSOURCE_PLLCLK
board=custom

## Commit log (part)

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2025-11-16 start
2025-11-17 peripherals and pinout
2025-11-17 finished schematic and started PCB
2025-11-18 finish schematic
2025-11-18 stuff
2025-11-18 start routing
2025-11-20 udpate routing
2025-11-21 finished PCB
2025-11-21 photos
2025-11-21 changed buck
2025-11-21 different buck and heatbed
2025-11-23 images
2025-11-24 udpate pcb with fixes
2025-11-25 finish board and prod/case files
2025-11-25 better render
2025-11-25 add heatbed image
2025-11-25 update blender render
2025-11-25 update banner
2025-11-25 update bom and case
2025-11-27 udpate flyer
2025-11-29 fixed via sizing
2025-11-29 add in updated case
2025-12-05 update heatbed
2025-12-06 Correct heatbed dimensions in README
    Updated heatbed size in README from 400mm x 400mm and 200mm x 200mm to 120mm x 120mm.
2025-12-16 start disabling pins
2025-12-16 added speaker stuff and usb c pd driver
2025-12-16 lock
2025-12-16 add nfc
2025-12-16 nfc stuff
2025-12-17 add in knoib and fix nfc
2025-12-17 added in musicxml to custom speaker driver lol
2025-12-18 bluetooth init
2025-12-19 add in bluetooth
2025-12-25 add in oled
2025-12-26 add in ug82
2025-12-26 add in pages and menu
2025-12-26 home page
2025-12-26 add in title ethno font
2025-12-30 update code and flx haeter
2026-01-09 sutff
